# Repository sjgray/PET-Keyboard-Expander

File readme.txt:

PET/CBM Keyboard Expander
=========================

http://www.cbmsteve.ca
http://www.cbmsteve.ca/petexpkbd/index.html

This is a pcb to expand the PET/CBM keyboard from it's normal 10x8 matrix
to a larger 16x8 matrix. It does this by mounting on the keyboard's VIA
chip socket and using a SN74159 4-to-16 decoder to give the extra line.

The extra matrix lines can be used to support larger matrix keyboards
(such as the CBM-II 16x6 matrix or C128 keyboard etc) or just additional
key switches for added functions, or even a joystick interface.

To add additional keyboards to the PET/CBM it would also be necessary to
modify the PET's Editor ROM keyboard scanning routine and key matrix.
Look on Github for my own Editor ROM project.

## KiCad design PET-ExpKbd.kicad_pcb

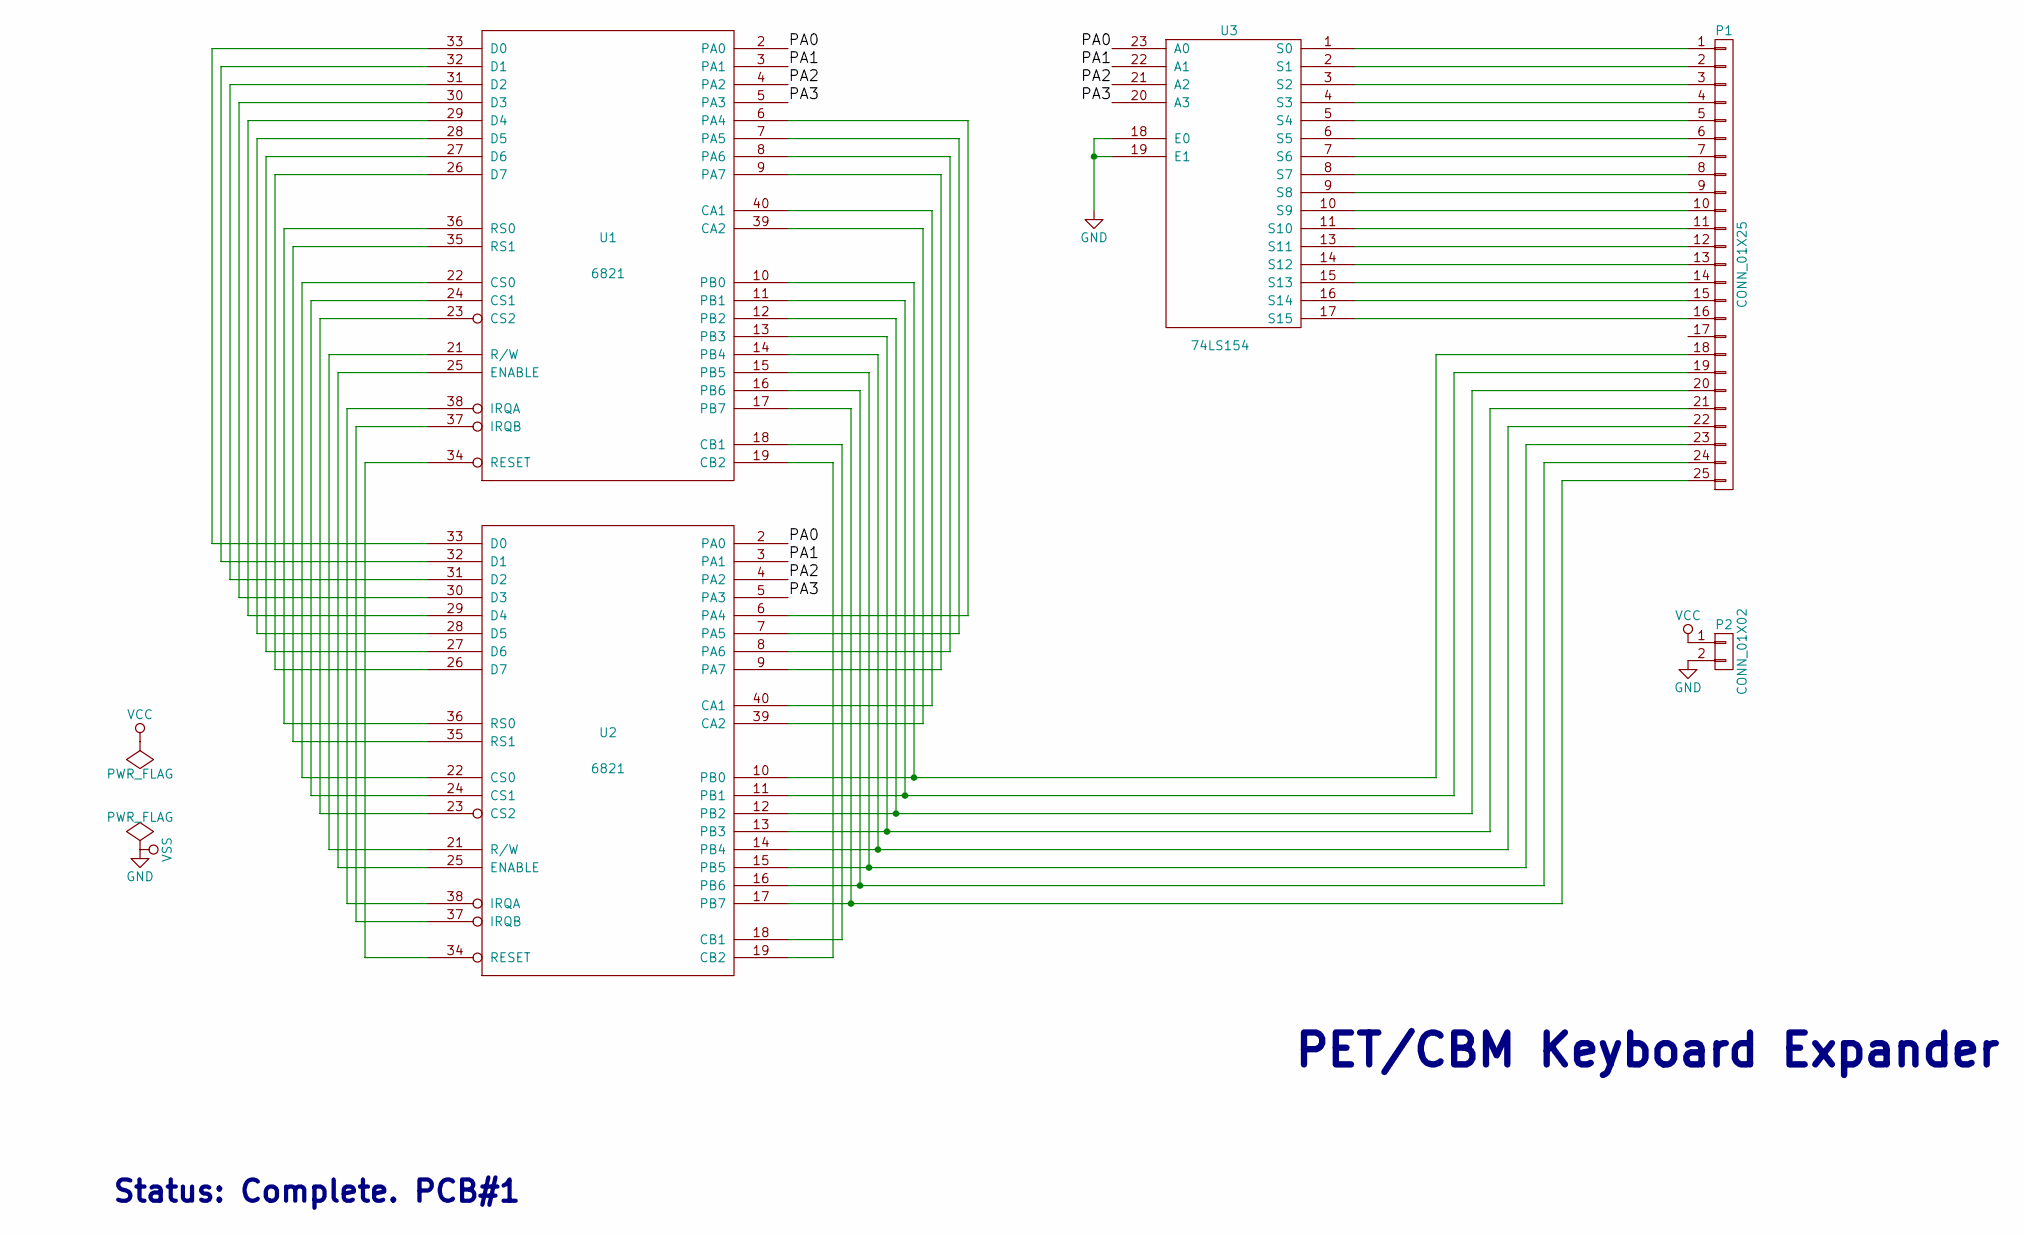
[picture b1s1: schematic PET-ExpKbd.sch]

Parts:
P1: CONN_01X25; Pin_Header_Straight_1x25
P2: CONN_01X02; Pin_Header_Straight_1x02
U1, U2: 6821; DIP-40_W15.24mm
U3: 74LS154; DIP-24_W15.24mm

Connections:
/PA0: U1.2 (PA0), U2.2 (PA0), U3.23 (A0)
/PA1: U1.3 (PA1), U2.3 (PA1), U3.22 (A1)
/PA2: U1.4 (PA2), U2.4 (PA2), U3.21 (A2)
/PA3: U1.5 (PA3), U2.5 (PA3), U3.20 (A3)
GND: P2.2, U1.1 (VSS), U2.1 (VSS), U3.12 (GND), U3.18 (E0), U3.19 (E1)
unnamed: P1.1, U3.1 (S0)
unnamed: P1.2, U3.2 (S1)
unnamed: P1.3, U3.3 (S2)
unnamed: P1.4, U3.4 (S3)
unnamed: P1.5, U3.5 (S4)
unnamed: P1.6, U3.6 (S5)
unnamed: P1.7, U3.7 (S6)
unnamed: P1.8, U3.8 (S7)
unnamed: P1.9, U3.9 (S8)
unnamed: P1.10, U3.10 (S9)
unnamed: P1.11, U3.11 (S10)
unnamed: P1.12, U3.13 (S11)
unnamed: P1.13, U3.14 (S12)
unnamed: P1.14, U3.15 (S13)
unnamed: P1.15, U3.16 (S14)
unnamed: P1.16, U3.17 (S15)
unnamed: P1.18, U1.10 (PB0), U2.10 (PB0)
unnamed: P1.19, U1.11 (PB1), U2.11 (PB1)
unnamed: P1.20, U1.12 (PB2), U2.12 (PB2)
unnamed: P1.21, U1.13 (PB3), U2.13 (PB3)
unnamed: P1.22, U1.14 (PB4), U2.14 (PB4)
unnamed: P1.23, U1.15 (PB5), U2.15 (PB5)
unnamed: P1.24, U1.16 (PB6), U2.16 (PB6)
unnamed: P1.25, U1.17 (PB7), U2.17 (PB7)
unnamed: U1.6 (PA4), U2.6 (PA4)
unnamed: U1.7 (PA5), U2.7 (PA5)
unnamed: U1.8 (PA6), U2.8 (PA6)
unnamed: U1.9 (PA7), U2.9 (PA7)
unnamed: U1.18 (CB1), U2.18 (CB1)
unnamed: U1.19 (CB2), U2.19 (CB2)
unnamed: U1.21 (R/W), U2.21 (R/W)
unnamed: U1.22 (CS0), U2.22 (CS0)
unnamed: U1.23 (CS2), U2.23 (CS2)
unnamed: U1.24 (CS1), U2.24 (CS1)
unnamed: U1.25 (ENABLE), U2.25 (ENABLE)
unnamed: U1.26 (D7), U2.26 (D7)
unnamed: U1.27 (D6), U2.27 (D6)
unnamed: U1.28 (D5), U2.28 (D5)
unnamed: U1.29 (D4), U2.29 (D4)
unnamed: U1.30 (D3), U2.30 (D3)
unnamed: U1.31 (D2), U2.31 (D2)
unnamed: U1.32 (D1), U2.32 (D1)
unnamed: U1.33 (D0), U2.33 (D0)
unnamed: U1.34 (RESET), U2.34 (RESET)
unnamed: U1.35 (RS1), U2.35 (RS1)
unnamed: U1.36 (RS0), U2.36 (RS0)
unnamed: U1.37 (IRQB), U2.37 (IRQB)
unnamed: U1.38 (IRQA), U2.38 (IRQA)
unnamed: U1.39 (CA2), U2.39 (CA2)
unnamed: U1.40 (CA1), U2.40 (CA1)
VCC: P2.1, U1.20 (VCC), U2.20 (VCC), U3.24 (VCC)

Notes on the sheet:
PET/CBM Keyboard Expander
Status: Complete. PCB#1

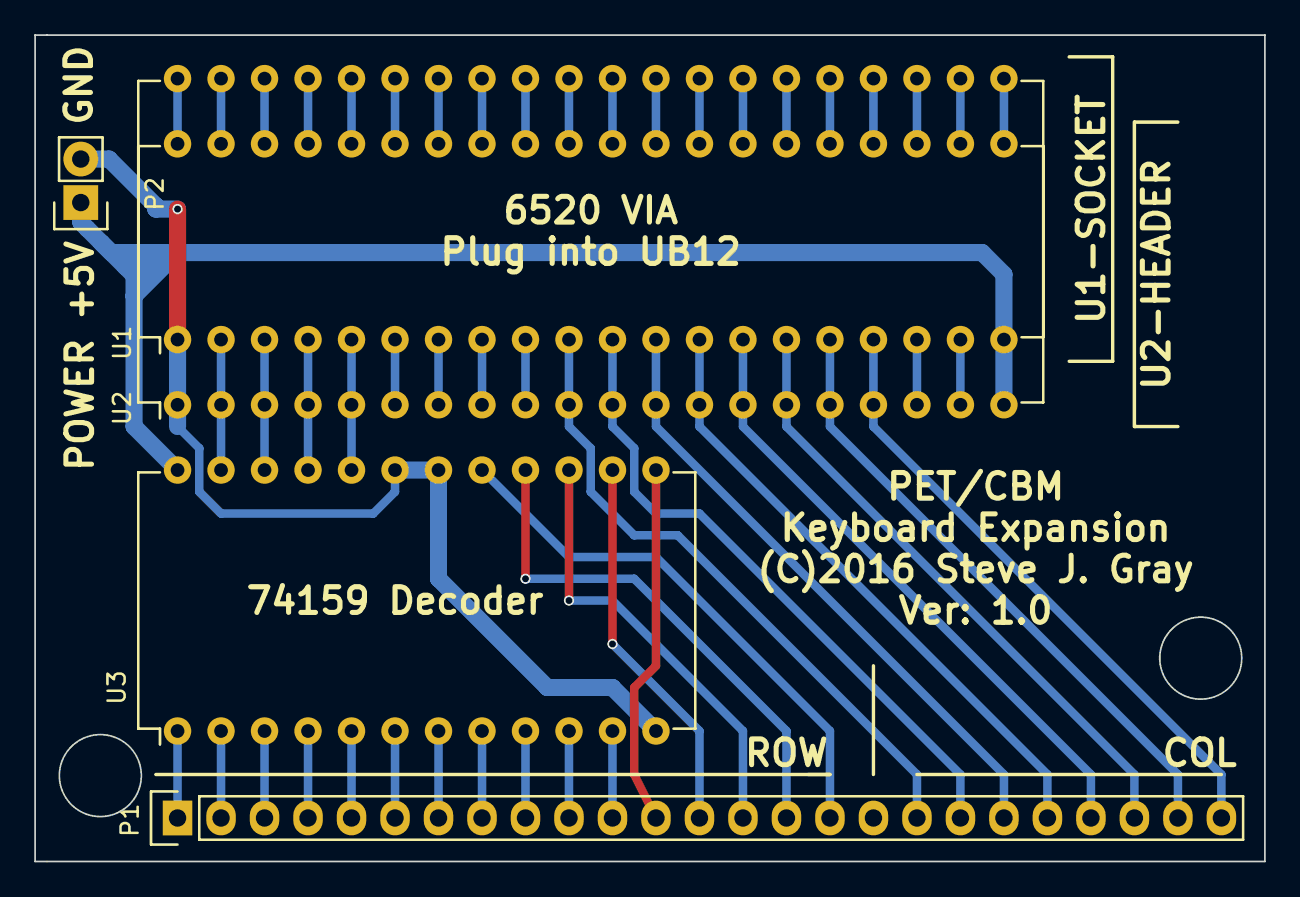
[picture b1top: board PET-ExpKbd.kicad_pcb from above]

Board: 2 copper layers, 71.8 x 48.3 mm, 5 parts (0 on the bottom side), 56 nets.

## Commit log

2020-12-13 :confetti_ball: Added .gitattributes & .gitignore files
2020-12-13 Initial Commit
    These are the original files from the 2016 initial design. They use an
    older version of Kicad. Also the 74159 chip should be used in place of
    the 74154 for proper operation (it has the same pinout).
2020-12-13 Add pics and link to web project
    Add some picture and web link
2025-01-15 Update webpage
    http://www.cbmsteve.ca/

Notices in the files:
PET-ExpKbd.kicad_pcb:
(C)2016 Steve J. Gray
